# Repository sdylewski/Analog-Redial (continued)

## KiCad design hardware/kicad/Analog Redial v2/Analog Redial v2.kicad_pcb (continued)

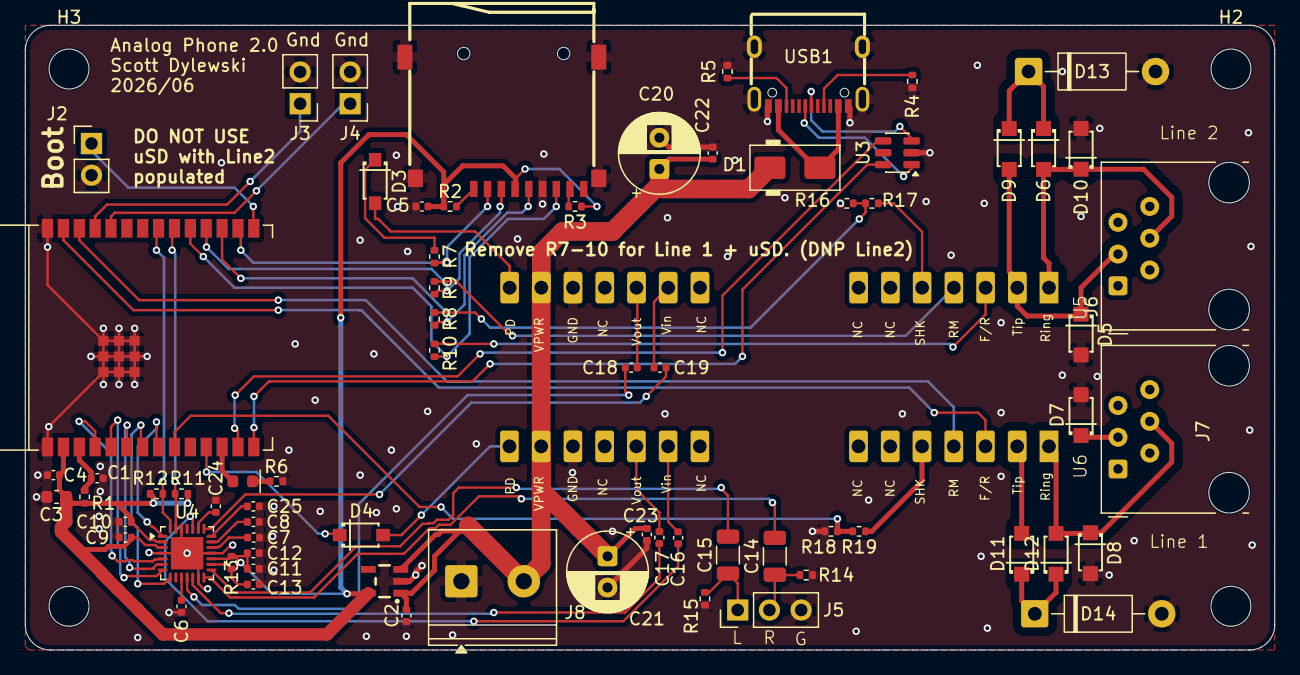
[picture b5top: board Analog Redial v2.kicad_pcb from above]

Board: 2 copper layers, 100.0 x 50.0 mm, 77 parts (0 on the bottom side), 65 nets.

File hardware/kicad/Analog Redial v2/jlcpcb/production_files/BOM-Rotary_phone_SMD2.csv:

Comment,Designator,Footprint,LCSC,Quantity
0R,"R10,R7,R8,R9",R_0402_1005Metric,C17168,4
100nF,"C10,C12,C13,C17,C18,C22,C23,C24,C25,C4,C5,C9",C_0402_1005Metric,C1525,12
100uF,"C14,C15",C_1206_3216Metric,C15008,2
10R,R13,R_0402_1005Metric,C25077,1
10k,"R1,R17,R19,R2,R3",R_0402_1005Metric,C25744,5
10nF,"C16,C19",C_0402_1005Metric,C15195,2
10uF,"C11,C2",C_0402_1005Metric,C15525,2
15k,"R16,R18",R_0402_1005Metric,C25756,2
1N4007,"D10,D11,D12,D5,D6,D7,D8,D9",1N4007W_C18199088,C18199088,8
1N4148,"D3,D4",1N4148W_C81598,C81598,2
1uF,"C1,C6,C7,C8",C_0402_1005Metric,C52923,4
220R,R6,R_0402_1005Metric,C25091,1
22uF,C3,C_0603_1608Metric,C59461,1
4.7k,"R11,R12",R_0402_1005Metric,C25900,2
47k,"R14,R15",R_0402_1005Metric,C25792,2
5.1k,"R4,R5",R_0402_1005Metric,C25905,2
ES8388,U4,QFN-28-1EP_4x4mm_P0.45mm_EP2.6x2.6mm,C365736,1
Red,D2,LED_0603_1608Metric_Red,C2286,1
SS14,D1,D_SMA,C2480,1
TF-01A,Card1,TF-01A,C91145,1
TYPE-C_16PIN_2MD_073,USB1,TYPE-C_16PIN_2MD_073,C2765186,1
PINHD_1x3_Male,J5,PinHeader_1x03_P2.54mm_Vertical,,1
PINHD_1x2_Male,J2,PinHeader_1x02_P2.54mm_Vertical,,1
RJ12,J7,RJ12_Amphenol_54601-x06_Horizontal,,1
USBLC6-2SC6,U3,SOT-23-6,,1
PINHD_1x2_Male,J3,PinHeader_1x02_P2.54mm_Vertical,,1
ESP32-C6-WROOM-1,U2,ESP32-C6-WROOM-1,,1
470uF 16V,C20,CP_Radial_D6.3mm_P2.50mm,,1
ME6211C33M5G-N,U1,SOT23-5,,1
PINHD_1x2_Male,J4,PinHeader_1x02_P2.54mm_Vertical,,1
RJ12,J6,RJ12_Amphenol_54601-x06_Horizontal,,1
AG1171,U6,AG1171_SIL,,1
D_Zener P6KE82,D14,D_DO-41_SOD81_P10.16mm_Horizontal,,1
D_Zener P6KE82,D13,D_DO-41_SOD81_P10.16mm_Horizontal,,1
AG1171,U5,AG1171_SIL,,1
470uF 16V,C21,CP_Radial_D6.3mm_P2.50mm,,1
MountingHole_M3,H4,MountingHole_3.2mm_M3,,1
MountingHole_M3,H3,MountingHole_3.2mm_M3,,1
MountingHole_M3,H2,MountingHole_3.2mm_M3,,1
MountingHole_M3,H1,MountingHole_3.2mm_M3,,1
Screw_Terminal_2_P5.00mm,J8,"TerminalBlock_Phoenix_PT-1,5-2-5.0-H_1x02_P5.00mm_Horizontal",,1

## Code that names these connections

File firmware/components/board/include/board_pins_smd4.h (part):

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 * ("Pin map (ESP32-C6-DevKitC-1, U1)", confirmed 2026-08-30) and
 * docs/hardware.md section 3. Genuinely different from board_pins_smd.h
 * (SMD2): moving the MCU carrier from a soldered WROOM-1 module to a
 * DevKitC-1 dev board freed up GPIO0/1/2 and remapped I2S there, which in
 * turn pushed line 0's SLIC control onto GPIO4-7 instead of SMD2's I2S
 * pins there. Two specific gotchas worth calling out because they're easy
 * to get backwards from memory or from SMD2's header:
 *
 *   - I2S pins are NOT the same GPIOs as SMD2 (compare BOARD_I2S_* below to
 *     board_pins_smd.h) -- SMD2 put I2S on GPIO0/4/5/6/7; here it's on
 *     GPIO0/1/2/10/11, freeing GPIO4-7 for line 0's SLIC.
 *   - The GPIO18-21 to signal mapping is NOT the same as SMD2's, even
 *     though both boards XOR the same four pins between the shared line's
 *     SLIC and a microSD socket: SMD2 pairs GPIO18 with PD/CS and GPIO21
 *     with F/R and MISO; this board pairs GPIO18 with F/R and MISO, and
 *     GPIO21 with PD and CS -- 18 and 21 are swapped. GPIO19 (SHK/CLK) and
 *     GPIO20 (RM/MOSI) match SMD2. Confirmed against
 *     archive/hardware/smd4.md's J5 jumper table, not carried
 *     over from SMD2's header by assumption.
 *
 * No status LED on this board (GPIO11, SMD2's LED pin, is I2S BCLK here) --
 * BOARD_STATUS_LED is deliberately not defined; board.c's LED code is
 * gated on CONFIG_BOARD_TYPE_SMD2 specifically (not the general "is this
 * an SMD board" check) for exactly this reason, so it correctly no-ops on
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 * "Reference/silk numbering note" if cross-checking against the board
 * itself.
 *
 * Macro naming note: the shared GPIO18-21 group keeps the BOARD_LINE2_PIN_*
 * prefix board.c (board_hw_detect_evidence()) hardcodes by that exact
 * name, even though this board's own documentation calls that same shared
 * line "line 1" -- a naming holdover from SMD2 (where the shared line
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/* The dual MCU footprint swaps pads 12/13 <-> 19/20 between the real
 * Espressif module and the AliExpress clone (archive/hardware/
 * smd5.md). The I2S_MCLK and SD_CD nets sit on pads 12/13,
 * which are GPIO2/3 on the real module but the clone's GPIO12/13 -- the
 * native-USB pins, freed up by board_early_pin_init() before audio starts. */
#define BOARD_I2S_MCLK    GPIO_NUM_12
#else
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
#if BOARD_LINE1_ON_EXPANDER
/* ---- SMD6: line 1's SLIC (U3) on a TCA9534A (U6, A0-A2 to GND). P4-P7 are the
 * spare pins on J10. GPIO18-21 above are the microSD card's alone. ---- */
#define BOARD_EXP_I2C_ADDR 0x38
#define BOARD_EXP_BIT_FR   0
#define BOARD_EXP_BIT_RM   1
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 * like this one until now, that doesn't define this macro).
 *
 * NOTE: as of the last design-doc update before this board was fabricated,
 * the GPIO3-to-Card1-pin-9 schematic net was still marked "planned, not
 * yet drawn". Confirm this actually reads a real card-detect signal (not
 * floating) during bring-up before trusting it, same as every other pin
 * on a first-fabrication board. */
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#define BOARD_UART_RX     GPIO_NUM_17

/* Bring-up/bench-only: BM64 MFB/RST_N/P2_0 control, for boards that have
 * temporarily wired a BM64 companion module to the same GPIO18-20 pads line
 * 1's SLIC/microSD would otherwise use (see the shared-pad comment above).
 * These #defines exist on every SMD4 board unconditionally (harmless if
 * unused), but the pins themselves are only safe to actually drive when
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 * fixed resistor instead and has no GPIO control over any of these three. */
#if CONFIG_BOARD_TYPE_SMD5 || CONFIG_BOARD_TYPE_SMD5_CHEAP || \
    CONFIG_BOARD_TYPE_SMD6
/* SMD5 gives MFB a pin of its own on the expanded J12 header: GPIO15, the
 * only genuinely spare pin on this pin map (GPIO8 drives the DevKit's RGB
 * LED, GPIO9 is the download-mode strap -- MFB's pull-down there would boot
 * the board into download mode every time). GPIO15 is a strapping pin too,
 * but it only selects the JTAG source and only when an eFuse that ships
 * unburned is set, so an external 100k pull-down on it is harmless.
 * Because it's dedicated, MFB works on a 2-line/microSD board as well --
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#define BOARD_BT_MFB_PIN  GPIO_NUM_15
#define BOARD_BT_MFB_DEDICATED 1
#else
#define BOARD_BT_MFB_PIN  BOARD_LINE2_PIN_FR_MISO  /* GPIO18 */
#endif
#define BOARD_BT_RST_PIN  BOARD_LINE2_PIN_SHK_SCLK /* GPIO19 */
#define BOARD_BT_P20_PIN  BOARD_LINE2_PIN_RM_MOSI  /* GPIO20 */

/* No status LED on this board -- BOARD_STATUS_LED intentionally not
 * defined, see this file's own top-of-file comment. */
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/* Always returns line 1's real pins regardless of runtime config -- this is
 * just the pin map, not a claim that line 1 is actually populated/active.
 * Callers (ag1170's line-1 init) must check board_hw_config_get().num_lines
 * before actually configuring these as a SLIC; on a board where GPIO18-21
 * are wired to a microSD instead, driving them as SLIC control lines would
 * just be wrong, not merely unused. */
static inline board_line_pins_t board_line_pins(int line)
{
    if (line == 0) {
        return (board_line_pins_t){ BOARD_LINE0_SHK, BOARD_LINE0_FR,
                                    BOARD_LINE0_RM,  BOARD_LINE0_PD };
    }
    return (board_line_pins_t){ BOARD_LINE1_SHK, BOARD_LINE1_FR,
                                BOARD_LINE1_RM,  BOARD_LINE1_PD };
}

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
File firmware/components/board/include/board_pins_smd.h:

/*
 * board_pins_smd.h — Pin map for Analog Redial v2 (ESP32-C6-WROOM-1 + ES8388).
 *
 * Verified against hardware/kicad/Analog Redial v2/Analog Redial v2.kicad_sch
 * (U2 = ESP32-C6-WROOM-1, U4 = ES8388, U5/U6 = AG1171 SLICs).
 *
 * The PCB supports two build options on GPIO 18–21 (mutually exclusive):
 *
 *   A) Line 2 populated (U5 + J7)     → dual-line gateway, no microSD
 *   B) Line 2 DNP, microSD populated    → single-line + SPI SD card
 *
 * Same copper on all boards; stuffing / CONFIG selects behavior.
 * See archive/hardware/smd2.md.
 *
 * Firmware "line 0" is wired to the SLIC labeled U6 on the schematic (net
 * labels /Line1_SHK etc.), and "line 1" to U5 (/Line2_SHK etc.) — the
 * schematic's Line1/Line2 net-label convention is the reverse of the
 * Tip/Ring-based U5/U6 naming used in CLAUDE.md's clearance table. Double
 * check against silkscreen (which RJ12 is J6 vs J7) before wiring up phones
 * during bring-up so "line 0"/"line 1" in the console matches the jack you
 * plugged in.
 */
#pragma once

#include "driver/gpio.h"
#include "board_config.h"

/* Array-sizing width, NOT how many lines are actually active -- that's now
 * runtime (board_hw_config_get(), board.h), not a build-time Kconfig choice.
 * Matches AUDIO_NUM_LINES (audio.h) and telephony.c's own NLINES vs.
 * NLINES_ACTIVE split, which this project already used for exactly this
 * "array is always max width, active count varies" pattern before this
 * header caught up to it. Fixed at 2: this PCB never has more than 2 lines
 * regardless of build option. */
#define BOARD_NUM_LINES 2

/* ---- I2S (ES8388) ---- */
#define BOARD_I2S_MCLK    GPIO_NUM_0
#define BOARD_I2S_BCLK    GPIO_NUM_4
#define BOARD_I2S_LRCK    GPIO_NUM_5
#define BOARD_I2S_DOUT    GPIO_NUM_6
#define BOARD_I2S_DIN     GPIO_NUM_7

/* ---- I2C (ES8388, CE tied to GND -> 0x10) ---- */
#define BOARD_I2C_SDA     GPIO_NUM_22
#define BOARD_I2C_SCL     GPIO_NUM_23
#define BOARD_CODEC_I2C_ADDR 0x10

/* ---- Line 1 SLIC (always populated) ---- */
#define BOARD_LINE0_SHK   GPIO_NUM_1
#define BOARD_LINE0_FR    GPIO_NUM_2
#define BOARD_LINE0_RM    GPIO_NUM_3
#define BOARD_LINE0_PD    GPIO_NUM_10  /* GPIO14 not routed on WROOM-1 module */

/* ---- GPIO 18–21: Line 2 SLIC *or* microSD (same PCB pads, XOR populate) ----
 * Physical pins, unconditional -- board_hw_detect_evidence() (board.h)
 * samples all four before either peripheral claims them. Which *meaning*
 * applies (SLIC control vs. SPI) used to be a build-time Kconfig choice;
 * now it's board_hw_config_get() at runtime (board.h) -- both naming
 * schemes are defined unconditionally here since they're just two names for
 * the same four physical pins, and it's up to whichever driver actually
 * initializes them (ag1170's line 2, or sdcard_init()) to check the runtime
 * config first and only claim them if it's actually the one selected. */
#define BOARD_LINE2_PIN_PD_CS     GPIO_NUM_18
#define BOARD_LINE2_PIN_SHK_SCLK  GPIO_NUM_19
#define BOARD_LINE2_PIN_RM_MOSI   GPIO_NUM_20
#define BOARD_LINE2_PIN_FR_MISO   GPIO_NUM_21

#define BOARD_SD_CS       BOARD_LINE2_PIN_PD_CS
#define BOARD_SD_SCLK     BOARD_LINE2_PIN_SHK_SCLK
#define BOARD_SD_MOSI     BOARD_LINE2_PIN_RM_MOSI
#define BOARD_SD_MISO     BOARD_LINE2_PIN_FR_MISO

#define BOARD_LINE1_SHK   BOARD_LINE2_PIN_SHK_SCLK
#define BOARD_LINE1_FR    BOARD_LINE2_PIN_FR_MISO
#define BOARD_LINE1_RM    BOARD_LINE2_PIN_RM_MOSI
#define BOARD_LINE1_PD    BOARD_LINE2_PIN_PD_CS

#define BOARD_PD_LEVEL_RUN        0
#define BOARD_PD_LEVEL_POWERDOWN  1
#define BOARD_SHK_OFFHOOK_LEVEL   1

#define BOARD_UART_TX     GPIO_NUM_16
#define BOARD_UART_RX     GPIO_NUM_17

/* Status LED (D2 via R6 220R), active-high. */
#define BOARD_STATUS_LED  GPIO_NUM_11

typedef struct {
    gpio_num_t shk;
    gpio_num_t fr;
    gpio_num_t rm;
    gpio_num_t pd;
} board_line_pins_t;

/* Always returns line 1's real pins regardless of runtime config -- this is
 * just the pin *map*, not a claim that line 1 is actually populated/active.
 * Callers (ag1170's line-2 init) must check board_hw_config_get().num_lines
 * before actually configuring these as a SLIC; on a board where GPIO18-21
 * are wired to a microSD instead, driving them as SLIC control lines would
 * just be wrong, not merely unused. */
static inline board_line_pins_t board_line_pins(int line)
{
    if (line == 0) {
        return (board_line_pins_t){ BOARD_LINE0_SHK, BOARD_LINE0_FR,
                                    BOARD_LINE0_RM,  BOARD_LINE0_PD };
    }
    return (board_line_pins_t){ BOARD_LINE1_SHK, BOARD_LINE1_FR,
                                BOARD_LINE1_RM,  BOARD_LINE1_PD };
}
